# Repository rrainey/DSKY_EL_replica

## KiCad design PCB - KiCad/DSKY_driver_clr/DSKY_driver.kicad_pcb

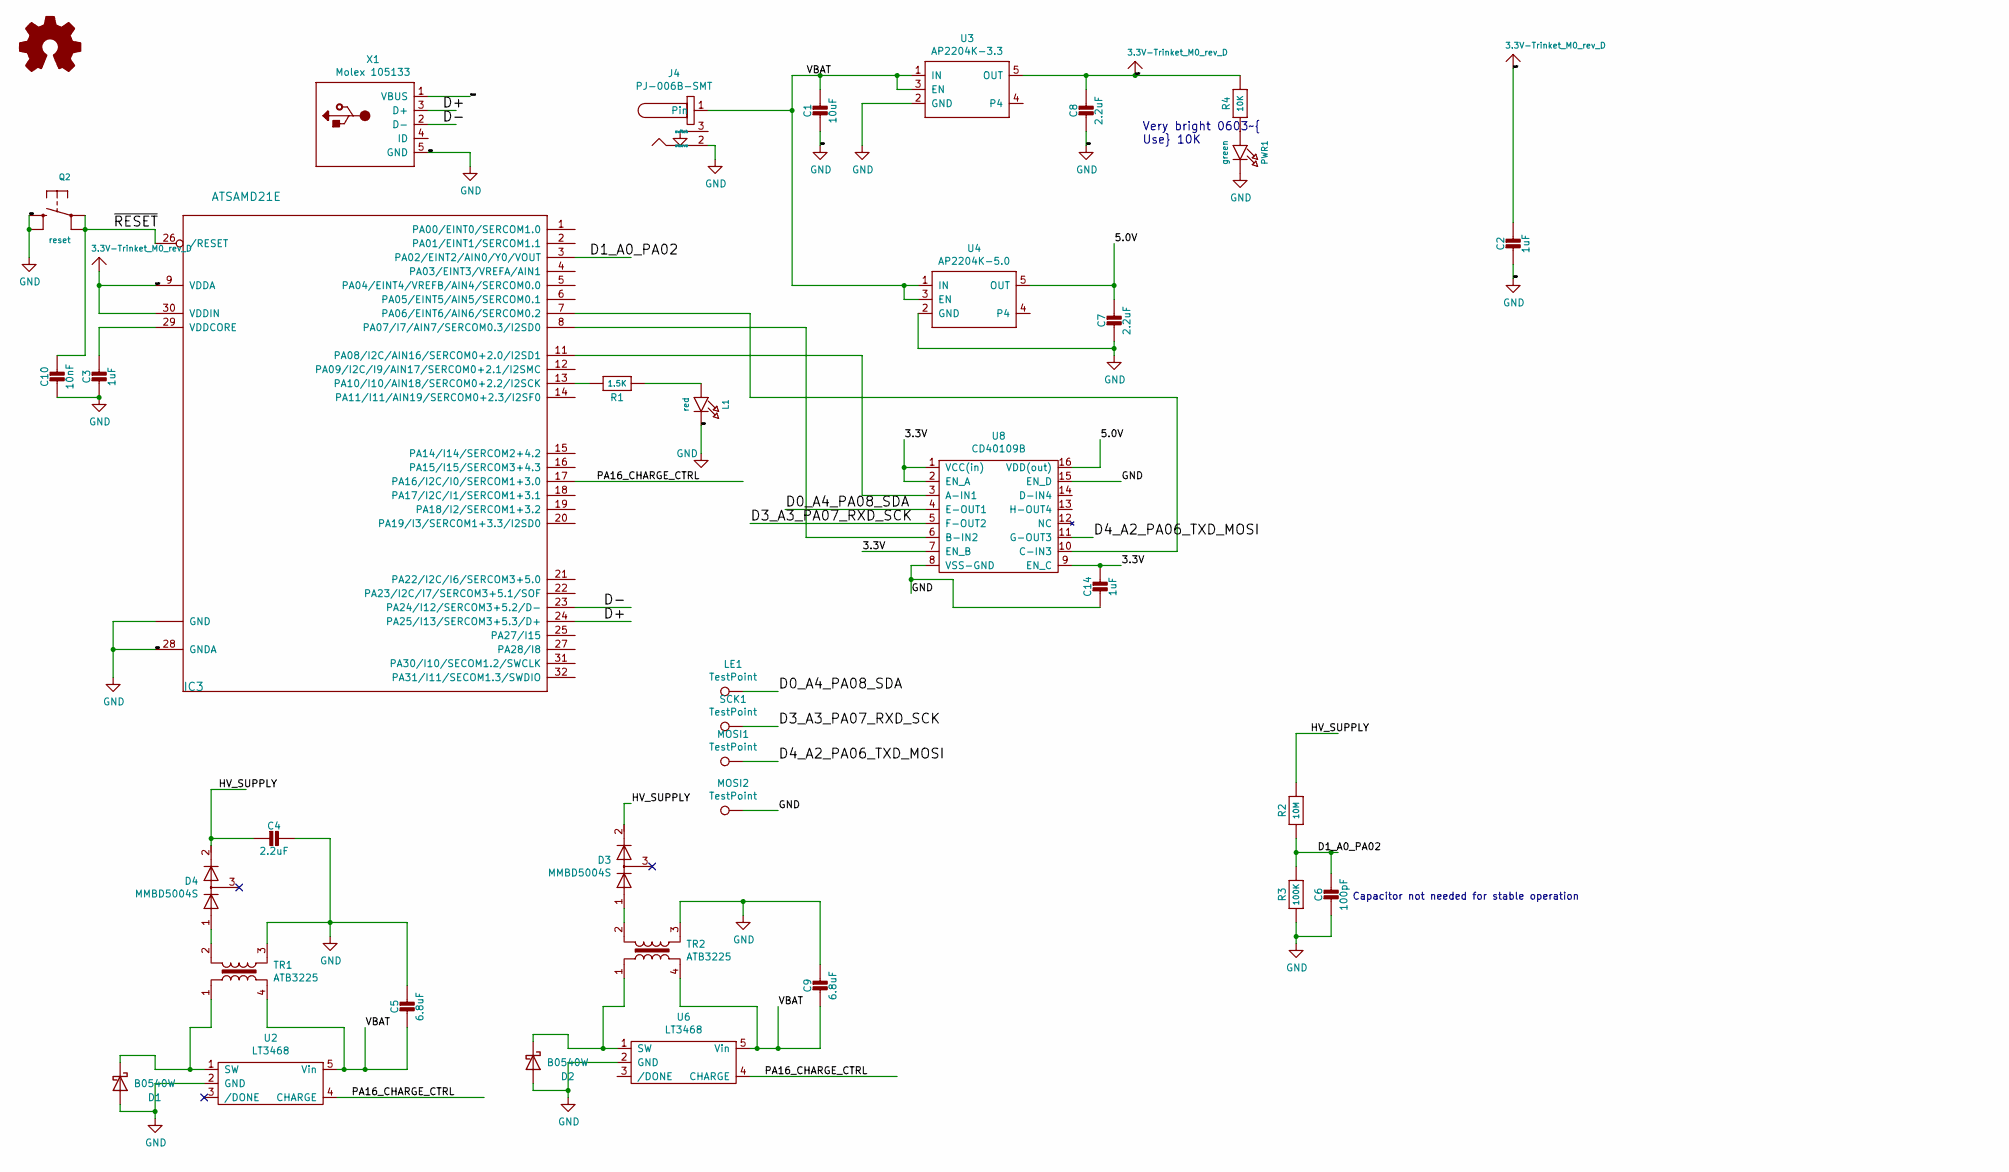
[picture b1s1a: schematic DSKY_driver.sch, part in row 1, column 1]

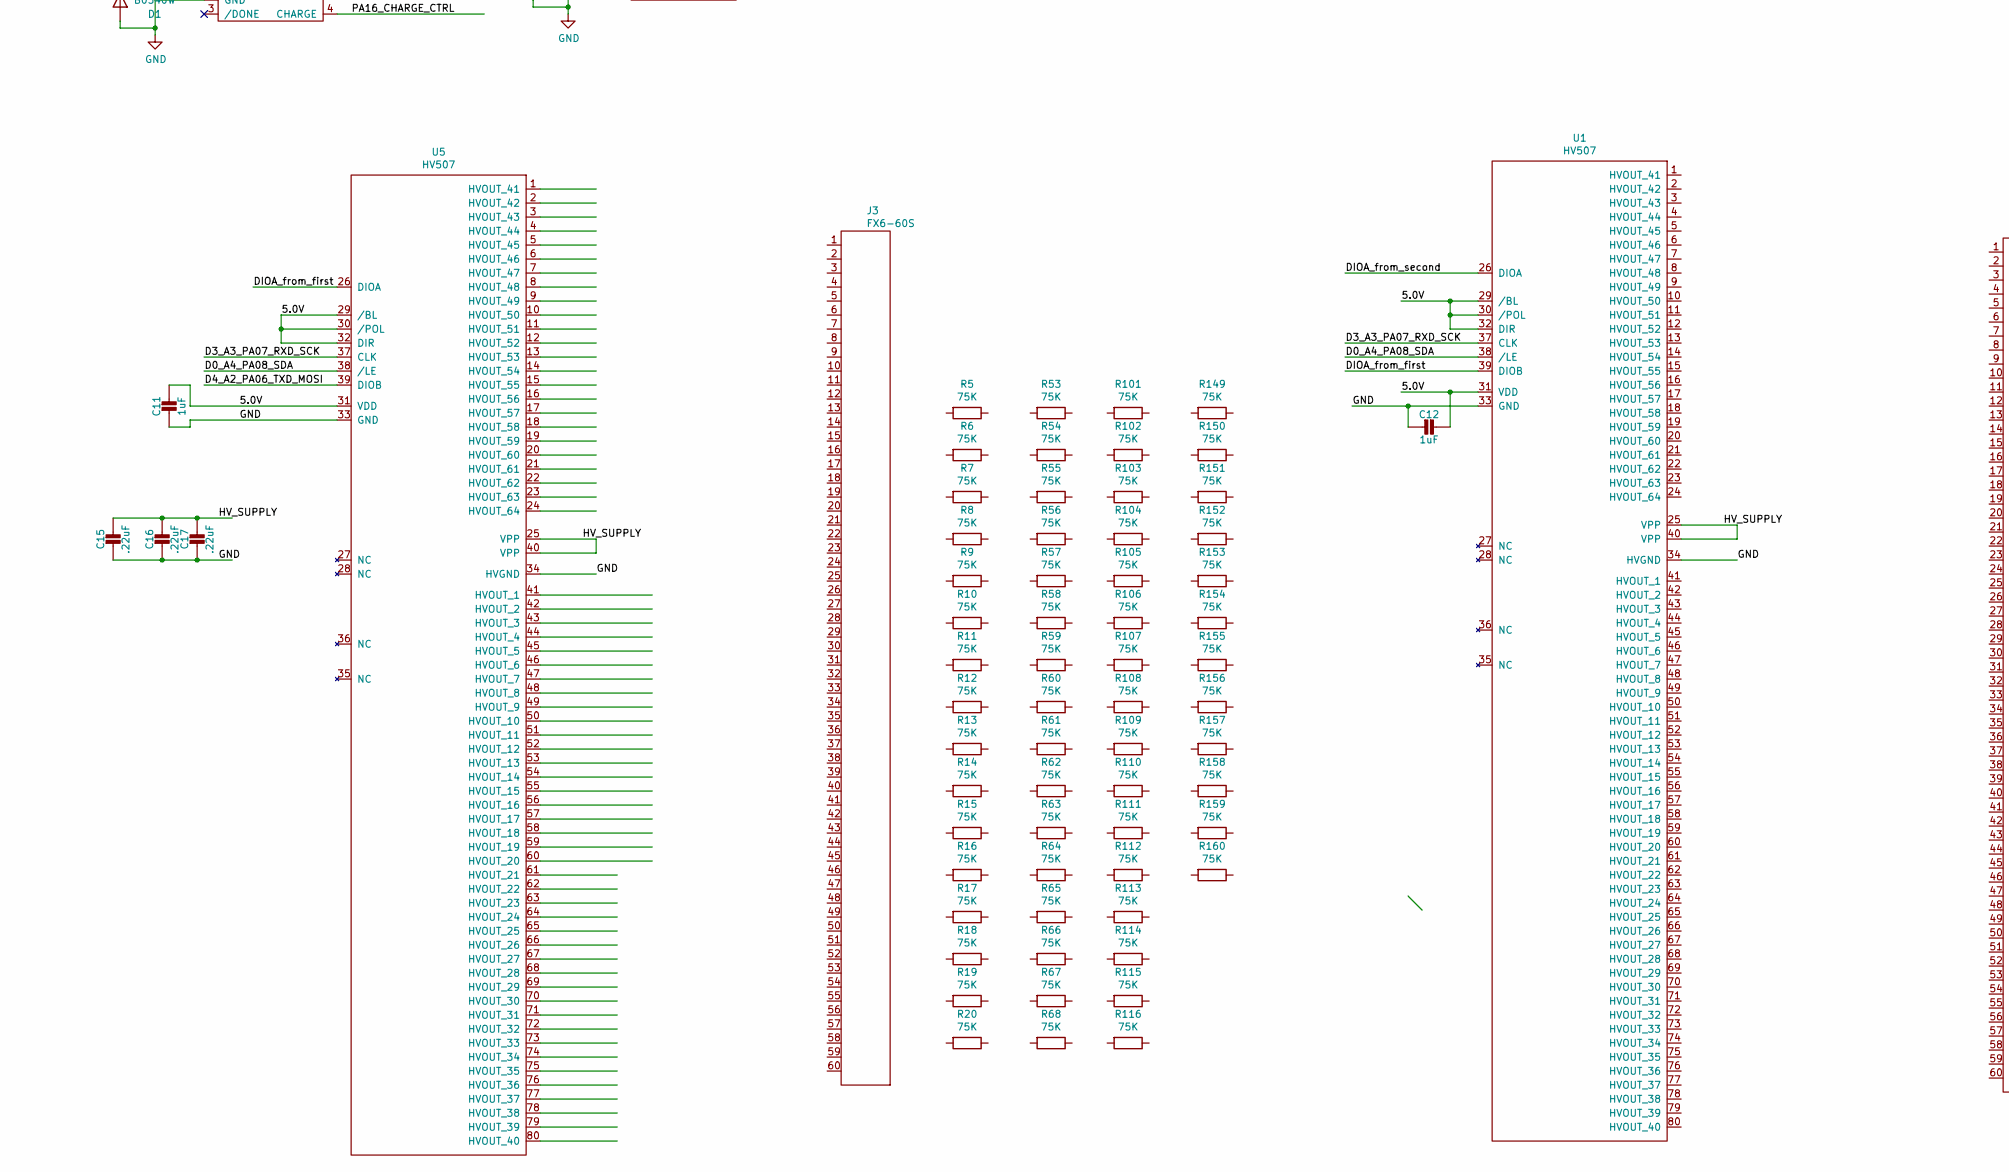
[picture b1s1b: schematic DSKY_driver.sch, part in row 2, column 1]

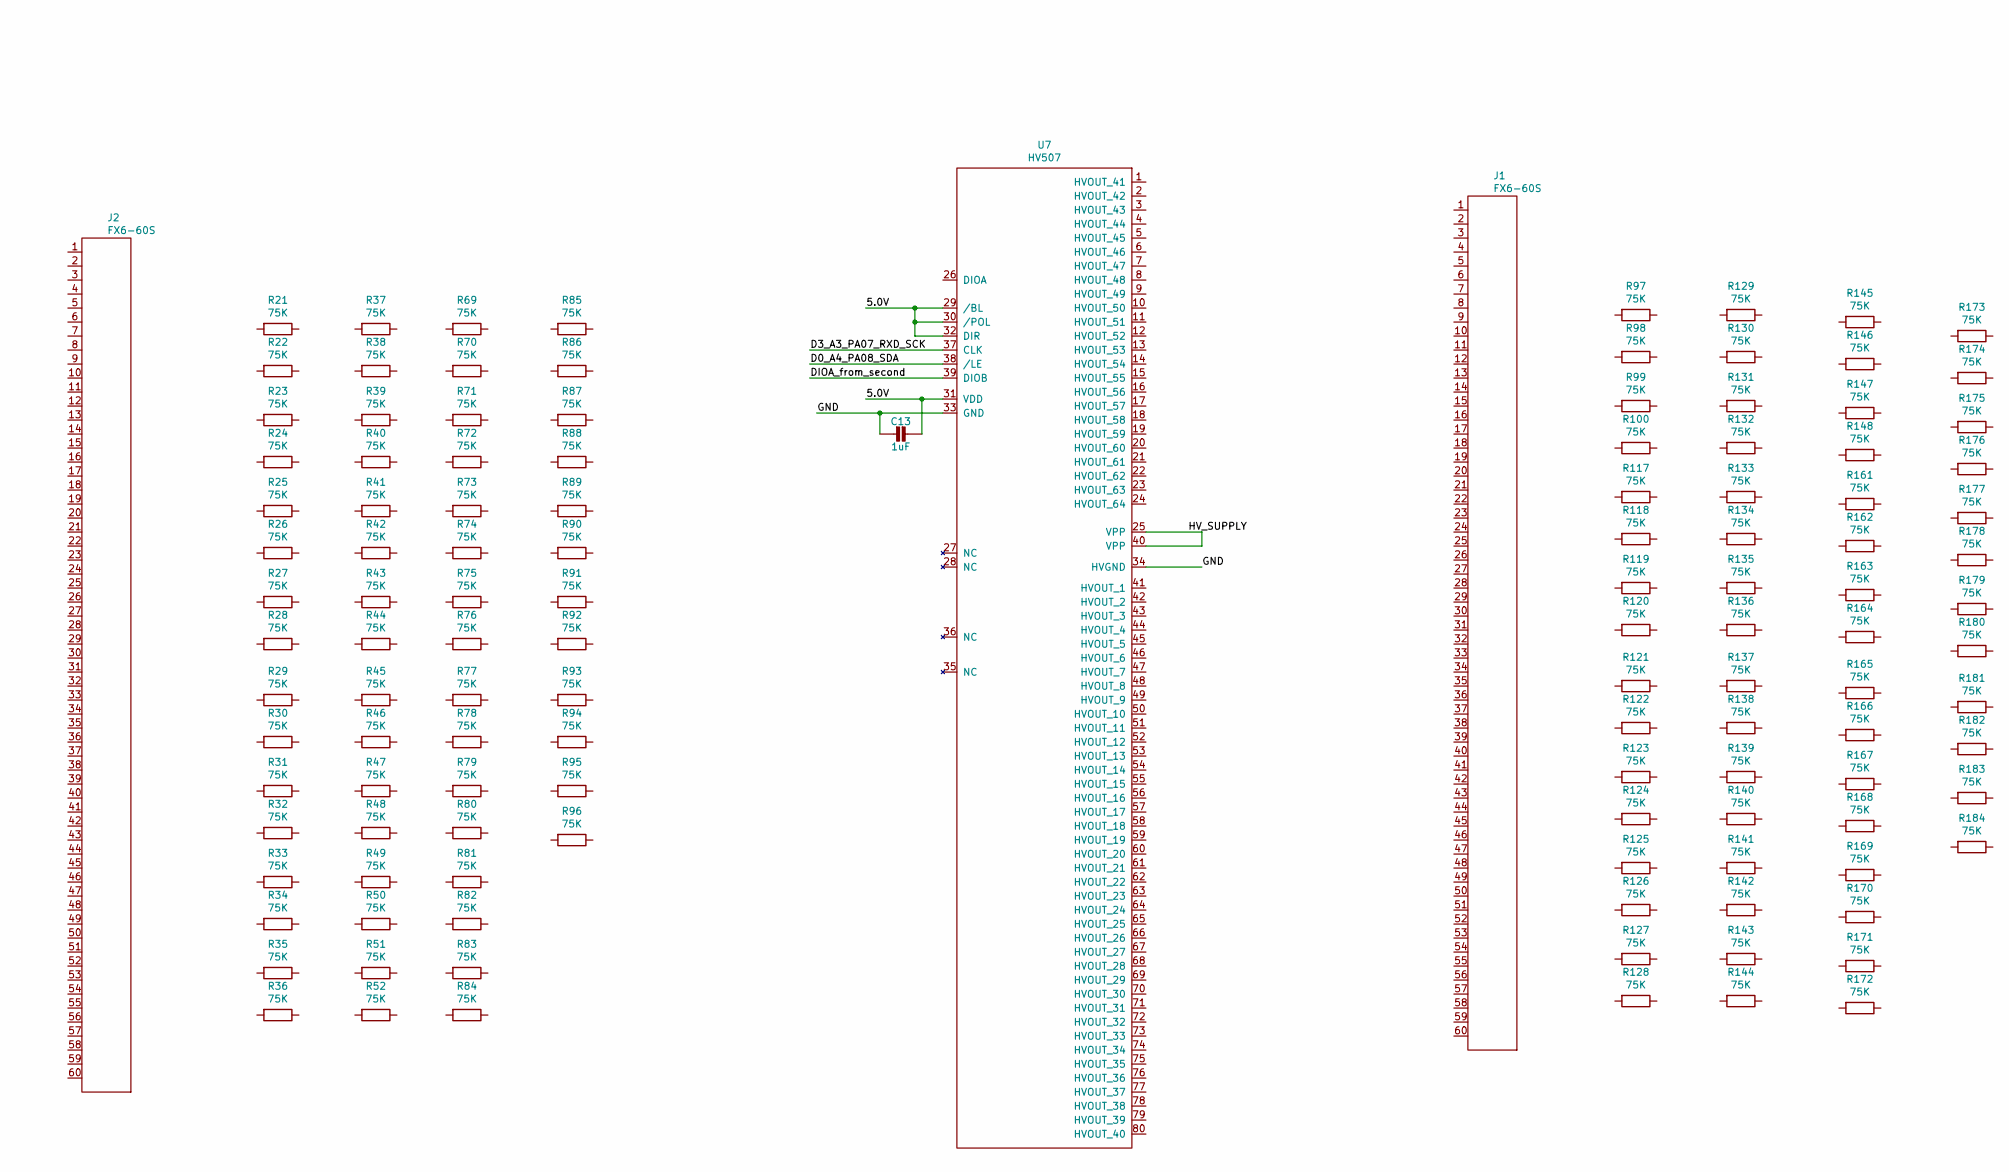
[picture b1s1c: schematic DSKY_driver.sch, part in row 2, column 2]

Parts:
C1: 10uF; 0805-NO
C2, C3, C11, C12, C13, C14: 1uF; 0603-NO
C4: 2.2uF; C_2220_5650Metric
C5, C9: 6.8uF; 0603-NO
C6: 100pF; 0603-NO
C7, C8: 2.2uF; 0805-NO
C10: 10nF; 0603-NO
C15, C16, C17: .22uF; C_1210_3225Metric
D1, D2: B0540W; D_SOD-123
D3, D4: MMBD5004S; SOT-23
IC3: ATSAMD21E; QFN32_5MM
J1, J2, J3: FX6-60S
J4: PJ-006B-SMT; CUI_PJ-006B-SMT_power_jack
L1: red; CHIPLED_0603_NOOUTLINE
LE1: TestPoint; TestPoint_Pad_D1.0mm
LOGO1: Logo_Open_Hardware_Small; OSHW-Logo_5.7x6mm_SilkScreen
MOSI1, MOSI2: TestPoint; TestPoint_Pad_D1.0mm
PWR1: green; CHIPLED_0603_NOOUTLINE
Q2: reset; BTN_KMR2_4.6X2.8
R1: 1.5K; 0603-NO
R2: 10M; 0603-NO
R3: 100K; 0603-NO
R4: 10K; 0603-NO
R5, R6, R7, R8, R9, R10, R11, R12, R13, R14, R15, R16, R17, R18, R19, R20, R21, R22, R23, R24, R25, R26, R27, R28, R29, R30, R31, R32, R33, R34, R35, R36, R37, R38, R39, R40, R41, R42, R43, R44, R45, R46, R47, R48, R49, R50, R51, R52, R53, R54, R55, R56, R57, R58, R59, R60, R61, R62, R63, R64, R65, R66, R67, R68, R69, R70, R71, R72, R73, R74, R75, R76, R77, R78, R79, R80, R81, R82, R83, R84, R85, R86, R87, R88, R89, R90, R91, R92, R93, R94, R95, R96, R97, R98, R99, R100, R101, R102, R103, R104, R105, R106, R107, R108, R109, R110, R111, R112, R113, R114, R115, R116, R117, R118, R119, R120, R121, R122, R123, R124, R125, R126, R127, R128, R129, R130, R131, R132, R133, R134, R135, R136, R137, R138, R139, R140, R141, R142, R143, R144, R145, R146, R147, R148, R149, R150, R151, R152, R153, R154, R155, R156, R157, R158, R159, R160, R161, R162, R163, R164, R165, R166, R167, R168, R169, R170, R171, R172, R173, R174, R175, R176, R177, R178, R179, R180, R181, R182, R183, R184: 75K; R_0201_0603Metric
SCK1: TestPoint; TestPoint_Pad_D1.0mm
TR1, TR2: ATB3225
U1, U5, U7: HV507; QFP-96_14x20_Pitch0.8mm
U2, U6: LT3468; SOT-23-5
U3: AP2204K-3.3; SOT-23-5
U4: AP2204K-5.0; SOT-23-5
U8: CD40109B; TSSOP-16_4.4x5mm_P0.65mm
X1: Molex 105133; molex_105133_vertical_USB

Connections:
3.3V: C2.1, C8.1, C14.1, IC3.9 (VDDA), IC3.30 (VDDIN), R4.2, U3.5 (OUT), U8.1 (VCC(in)), U8.2 (EN_A), U8.7 (EN_B), U8.9 (EN_C)
/5.0V: C7.1, C11.1, C12.1, C13.1, U1.29 (/BL), U1.30 (/POL), U1.31 (VDD), U1.32 (DIR), U4.5 (OUT), U5.29 (/BL), U5.30 (/POL), U5.31 (VDD), U5.32 (DIR), U7.29 (/BL), U7.30 (/POL), U7.31 (VDD), U7.32 (DIR), U8.16 (VDD(out))
/D0_A4_PA08_SDA: LE1.1, U1.38 (/LE), U5.38 (/LE), U7.38 (/LE), U8.4 (E-OUT1)
/D1_A0_PA02: C6.1, IC3.3 (PA02/EINT2/AIN0/Y0/VOUT), R2.1, R3.2
/D3_A3_PA07_RXD_SCK: SCK1.1, U1.37 (CLK), U5.37 (CLK), U7.37 (CLK), U8.5 (F-OUT2)
/D4_A2_PA06_TXD_MOSI: MOSI1.1, U5.39 (DIOB), U8.11 (G-OUT3)
/D+: IC3.24 (PA25/I13/SERCOM3+5.3/D+), X1.3 (D+)
/D-: IC3.23 (PA24/I12/SERCOM3+5.2/D-), X1.2 (D-)
/DIOA_from_first: U1.39 (DIOB), U5.26 (DIOA)
/DIOA_from_second: U1.26 (DIOA), U7.39 (DIOB)
/HV_SUPPLY: C4.2, C15.1, C16.1, C17.1, D3.2, D4.2, R2.2, U1.25 (VPP), U1.40 (VPP), U5.25 (VPP), U5.40 (VPP), U7.25 (VPP), U7.40 (VPP)
/PA16_CHARGE_CTRL: IC3.17 (PA16/I2C/I0/SERCOM1+3.0), U2.4 (CHARGE), U6.4 (CHARGE)
/VBAT: C1.1, C5.2, C9.2, J4.1, TR1.4, TR2.4, U2.5 (Vin), U3.1 (IN), U3.3 (EN), U4.1 (IN), U4.3 (EN), U6.5 (Vin)
/VBUS: X1.1 (VBUS)
/~RESET: C10.1, IC3.26 (/RESET), Q2.A, Q2.A' (P1)
GND: C1.2, C2.2, C3.2, C4.1, C5.1, C6.2, C7.2, C8.2, C9.1, C10.2, C11.2, C12.2, C13.2, C14.2, C15.2, C16.2, C17.2, D1.2 (A), D2.2 (A), IC3.10 (GND), IC3.28 (GNDA), IC3.33 (GND), J4.2 (sleeve), L1.C, MOSI2.1, PWR1.C, Q2.B (S), Q2.B' (S1), R3.1, TR1.3, TR2.3, U1.33 (GND), U1.34 (HVGND), U2.2 (GND), U3.2 (GND), U4.2 (GND), U5.33 (GND), U5.34 (HVGND), U6.2 (GND), U7.33 (GND), U7.34 (HVGND), U8.8 (VSS-GND), U8.15 (EN_D), X1.5 (GND), X1.6 (GND), X1.7 (GND), X1.8 (GND)
unnamed: C3.1, IC3.29 (VDDCORE)
unnamed: D1.1 (K), TR1.1, U2.1 (SW)
unnamed: D2.1 (K), TR2.1, U6.1 (SW)
unnamed: D3.1, TR2.2
unnamed: D4.1, TR1.2
unnamed: IC3.7 (PA06/EINT6/AIN6/SERCOM0.2), U8.10 (C-IN3)
unnamed: IC3.8 (PA07/I7/AIN7/SERCOM0.3/I2SD0), U8.6 (B-IN2)
unnamed: IC3.11 (PA08/I2C/AIN16/SERCOM0+2.0/I2SD1), U8.3 (A-IN1)
unnamed: IC3.13 (PA10/I10/AIN18/SERCOM0+2.2/I2SCK), R1.2
unnamed: L1.A, R1.1
unnamed: PWR1.A, R4.1

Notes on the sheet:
Very bright 0603~ Use 10K
Capacitor not needed for stable operation

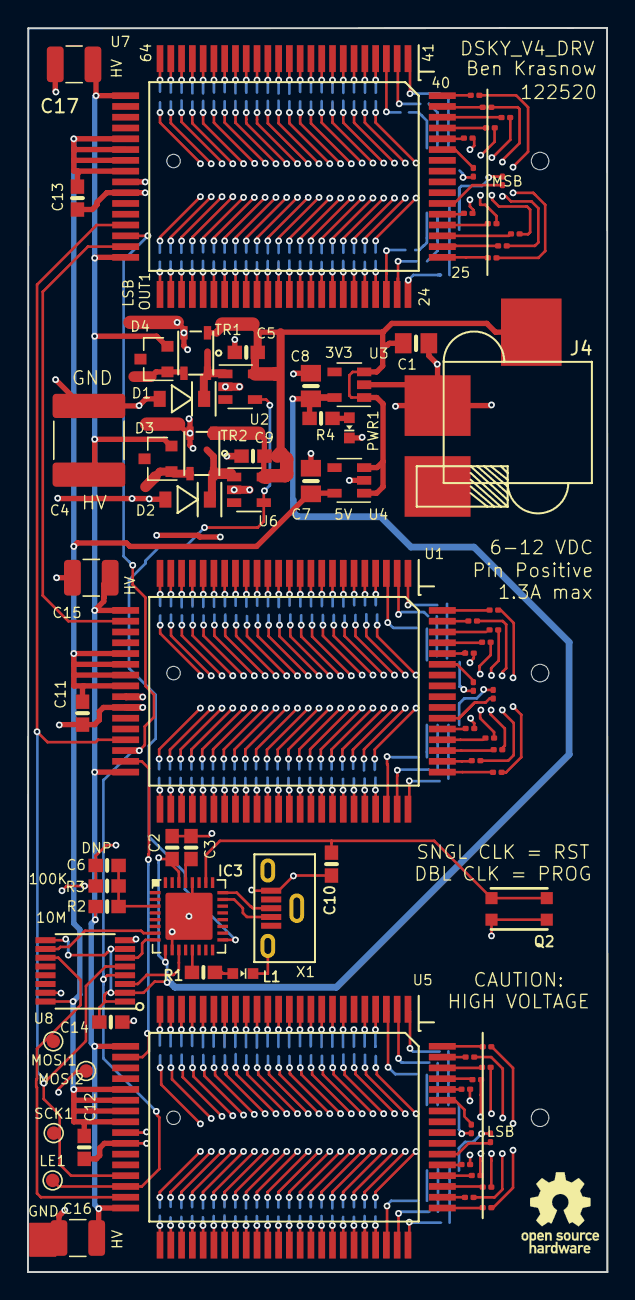
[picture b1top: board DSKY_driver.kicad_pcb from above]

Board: 2 copper layers, 43.0 x 92.3 mm, 229 parts (0 on the bottom side), 26 nets.

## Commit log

2020-12-20 Added draft "clr" - Current Limiting Resistor version of Driver board
2020-12-23 Fine tuning resistor placement
2020-12-24 more reorganization of resistor layout
2021-01-31 Latest draft PCB update
